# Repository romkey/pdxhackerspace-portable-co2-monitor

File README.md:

# Build Your Own Portable CO2 Monitor

Build Your Own Portable CO2 Monitor is a [PDX Hackerspace] project.

## Design Goals

- minimize cost
- true CO2 measurement
- choice of displays
- optional Home Assistant integration
- optional battery operation
- version that people who are inexperienced with soldering can build
- more integrated version for people who can assemble surface mount hardware
- open source software and hardware

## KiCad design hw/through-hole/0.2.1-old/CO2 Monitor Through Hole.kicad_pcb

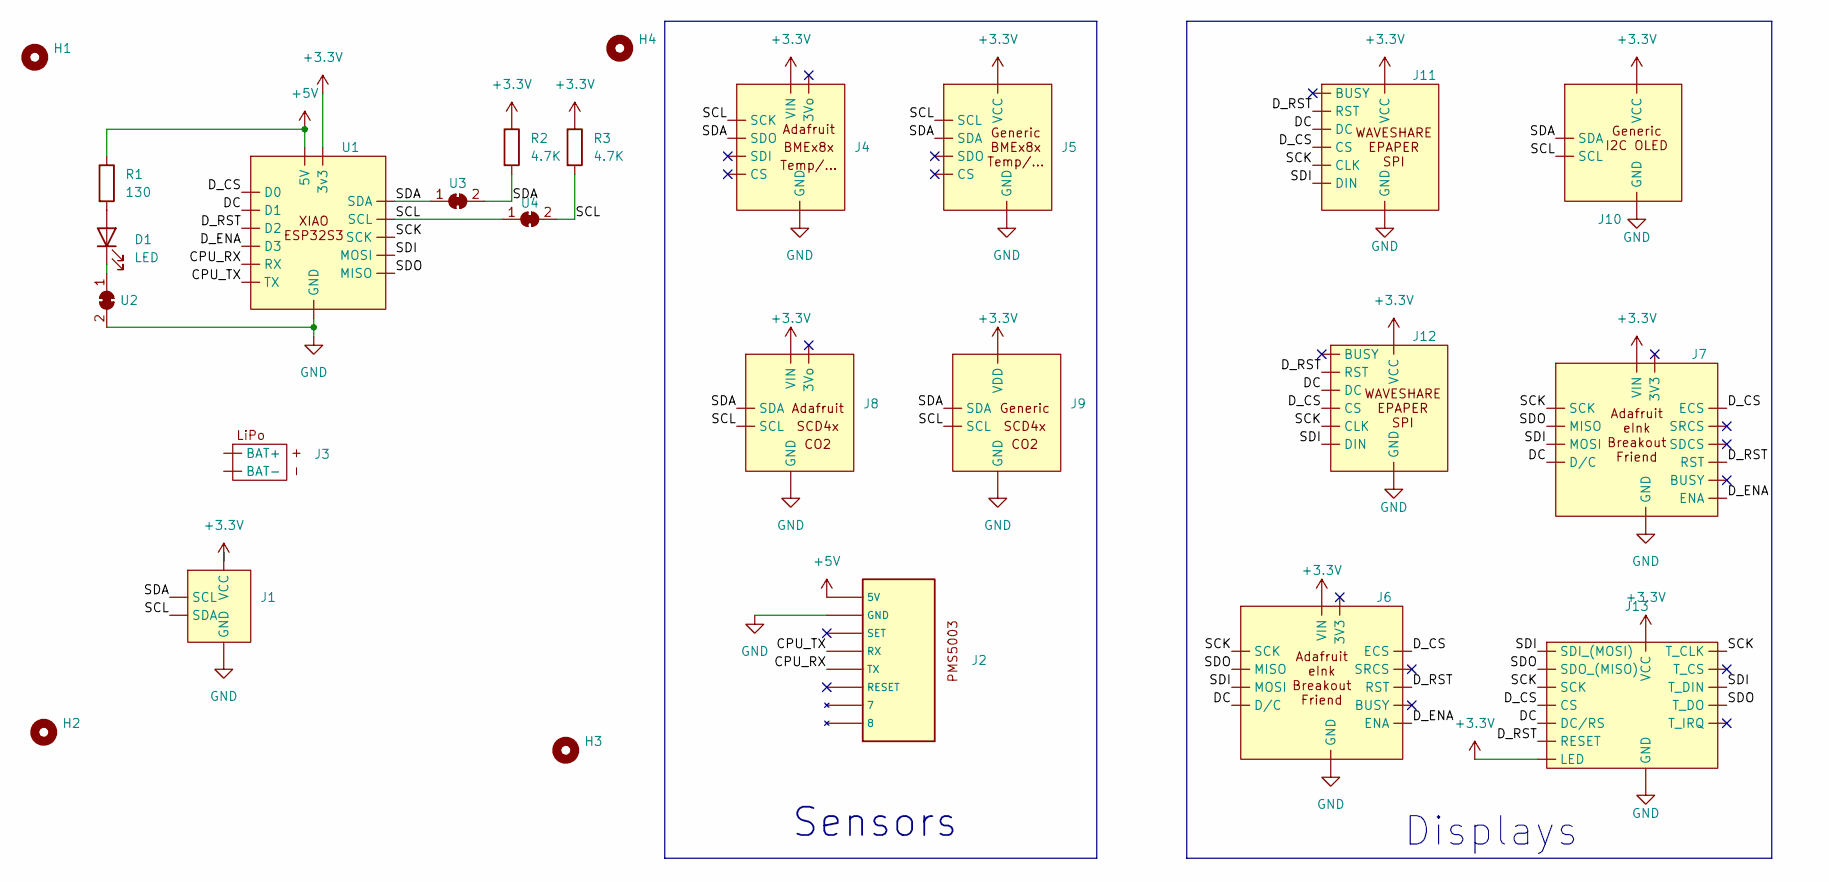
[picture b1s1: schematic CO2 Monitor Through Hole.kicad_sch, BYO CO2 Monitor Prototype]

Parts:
D1: LED; LED_D3.0mm
H1, H2, H3, H4: MountingHole; MountingHole_2.7mm_M2.5
J1: JST_SH_SM04B-SRSS-TB_1x04-1MP_P1.00mm_Horizontal
J2: PMS5003 Connector
J3: LiPo Connector
J4: Adafruit BMx8x Breakout
J5: Generic BMx8x Breakout
J6: Adafruit eInk Breakout Friend
J7: Adafruit eInk Breakout (GENERIC)
J8: Adafruit SCD4x Breakout
J9: Generic SCD4x Breakout
J10: Generic I2C OLED
J11: Wavshare ePaper SPI
J12: Waveshare ePaper SPI JST
J13: SPI_TFT_TOUCH
R1: 130; R_Axial_DIN0207_L6.3mm_D2.5mm_P7.62mm_Horizontal
R2, R3: 4.7K; R_Axial_DIN0207_L6.3mm_D2.5mm_P7.62mm_Horizontal
U1: Xiao ESP32S3
U2, U3, U4: SolderJumper-2_P1.3mm_Bridged_RoundedPad1.0x1.5mm

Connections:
+3.3V: J1.2 (VCC), J4.1 (VIN), J5.1 (VCC), J6.1 (VIN), J7.1 (VIN), J8.1 (VIN), J9.2 (VDD), J10.4 (VCC), J11.8 (VCC), J12.8 (VCC), J13.1 (VCC), J13.8 (LED), R2.1, R3.1, U1.12 (3v3)
+5V: J2.1 (5V), R1.1, U1.14 (5V)
/CPU_RX: J2.5 (TX), U1.8 (RX)
/CPU_TX: J2.4 (RX), U1.7 (TX)
/DC: J6.8 (D/C), J7.8 (D/C), J11.3 (DC), J12.3 (DC), J13.5 (DC/RS), U1.2 (D1)
/D_CS: J6.7 (ECS), J7.7 (ECS), J11.4 (CS), J12.4 (CS), J13.3 (CS), U1.1 (D0)
/D_ENA: J6.12 (ENA), J7.13 (ENA), U1.4 (D3)
/D_RST: J6.10 (RST), J7.11 (RST), J11.2 (RST), J12.2 (RST), J13.4 (RESET), U1.3 (D2)
/SCK: J6.4 (SCK), J7.4 (SCK), J11.5 (CLK), J12.5 (CLK), J13.7 (SCK), J13.10 (T_CLK), U1.9 (SCK)
/SCL: J1.3 (SDA), J4.4 (SCK), J5.3 (SCL), J8.4 (SCL), J9.3 (SCL), J10.2 (SCL), R3.2, U1.6 (SCL), U4.1 (A), U4.2 (B)
/SDA: J1.4 (SCL), J4.5 (SDO), J5.4 (SDA), J8.5 (SDA), J9.4 (SDA), J10.1 (SDA), R2.2, U1.5 (SDA), U3.1 (A), U3.2 (B)
/SDI: J6.6 (MOSI), J7.6 (MOSI), J11.6 (DIN), J12.6 (DIN), J13.6 (SDI_(MOSI)), J13.12 (T_DIN), U1.11 (MOSI)
/SDO: J6.5 (MISO), J7.5 (MISO), J13.9 (SDO_(MISO)), J13.13 (T_DO), U1.10 (MISO)
GND: J1.1 (GND), J2.2 (GND), J4.3 (GND), J5.2 (GND), J6.3 (GND), J7.3 (GND), J8.3 (GND), J9.1 (GND), J10.3 (GND), J11.7 (GND), J12.7 (GND), J13.2 (GND), U1.13 (GND), U2.2 (B)
unnamed: D1.2 (A), R1.2
unnamed: D1.1 (K), U2.1 (A)

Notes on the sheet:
Sensors
Displays

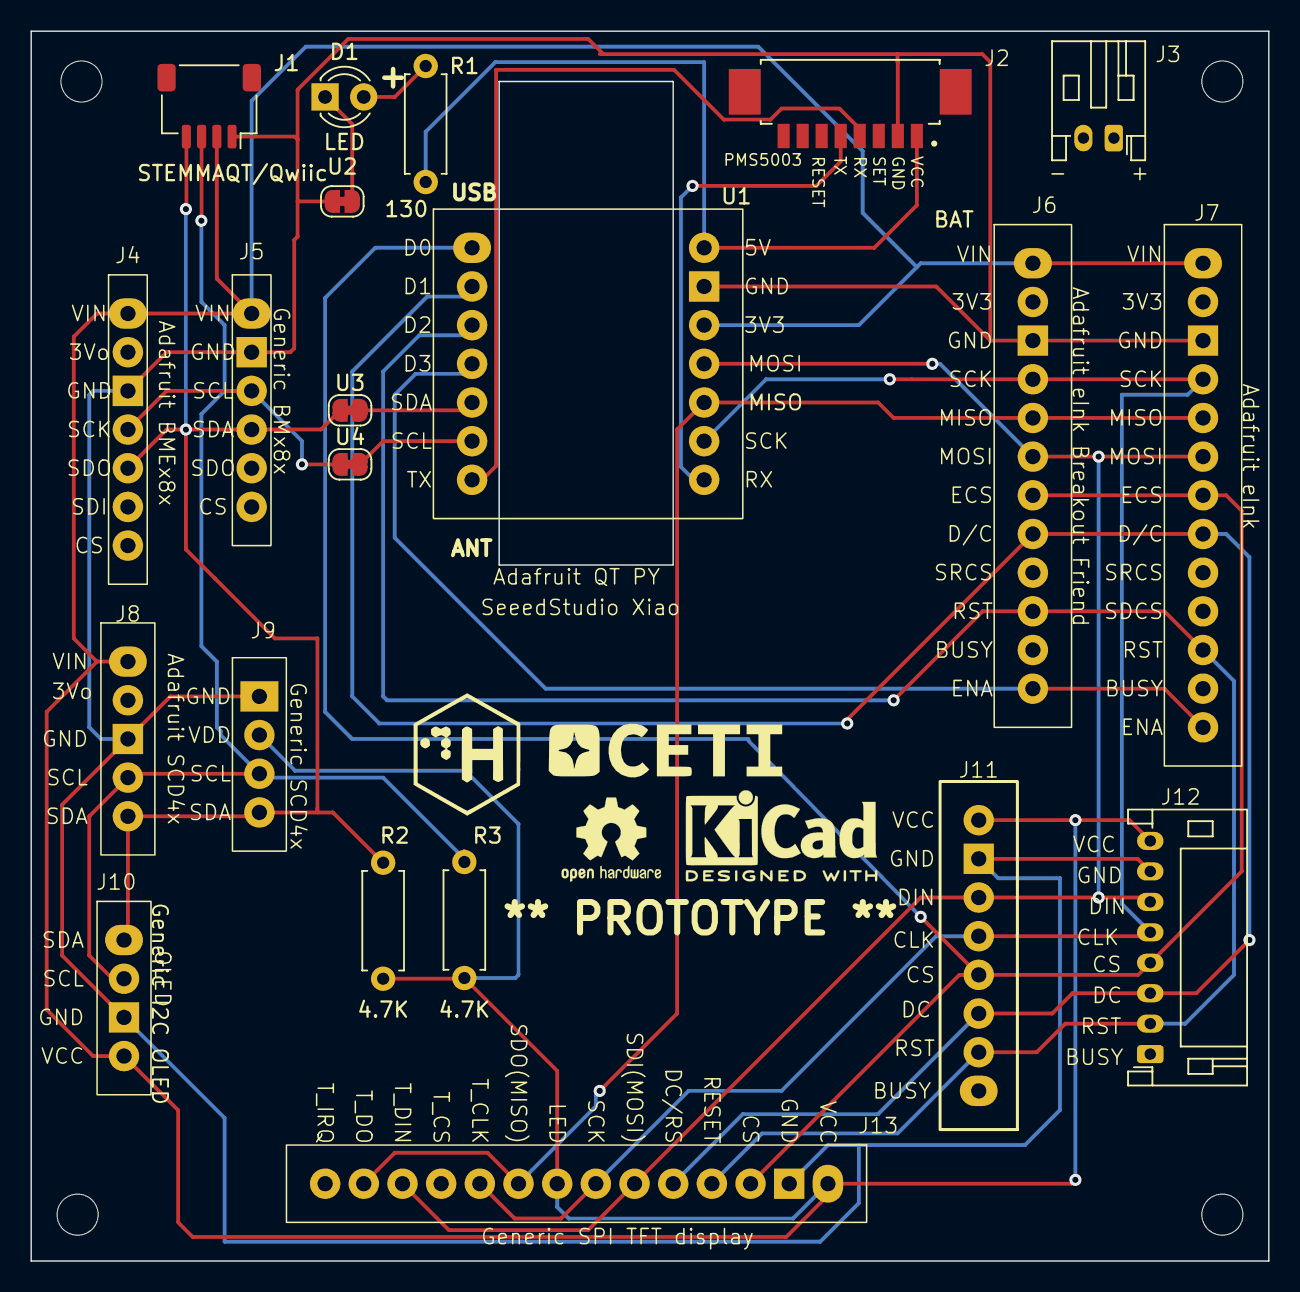
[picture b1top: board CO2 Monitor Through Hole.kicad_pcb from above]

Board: 2 copper layers, 81.3 x 80.8 mm, 25 parts (0 on the bottom side), 16 nets.

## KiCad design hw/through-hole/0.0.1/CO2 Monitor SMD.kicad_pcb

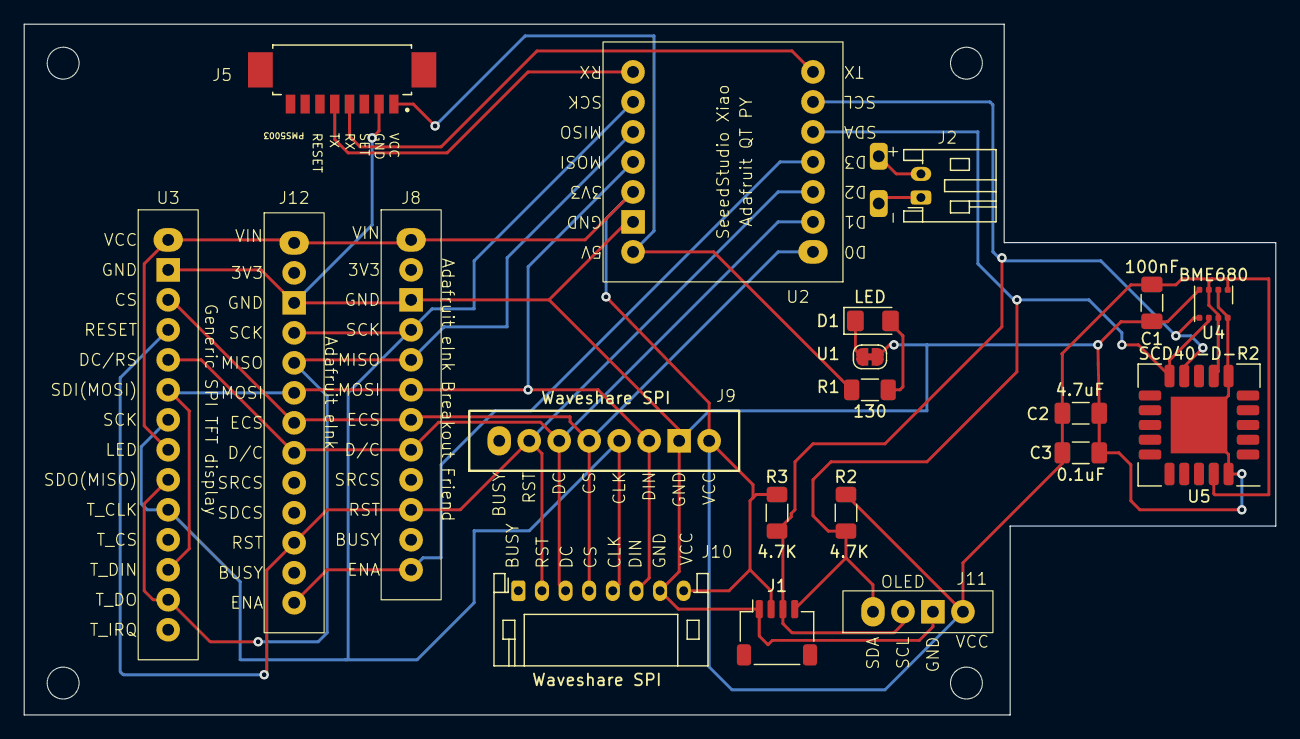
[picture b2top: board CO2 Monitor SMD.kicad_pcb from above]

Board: 2 copper layers, 106.0 x 58.5 mm, 25 parts (0 on the bottom side), 18 nets.

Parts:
C1: 100nF; C_1206_3216Metric_Pad1.33x1.80mm_HandSolder
C2: 4.7uF; C_1206_3216Metric_Pad1.33x1.80mm_HandSolder
C3: 0.1uF; C_1206_3216Metric_Pad1.33x1.80mm_HandSolder
D1: LED; LED_1206_3216Metric_Pad1.42x1.75mm_HandSolder
H1, H2, H3, H4: MountingHole; MountingHole_2.7mm_M2.5
J1: JST_SH_SM04B-SRSS-TB_1x04-1MP_P1.00mm_Horizontal
J2: LiPo Connector
J3: Conn_01x02; LiPo Pads
J5: PMS5003 Connector
J8: Adafruit eInk Breakout Friend
J9: Wavshare ePaper SPI
J10: Waveshare ePaper SPI JST
J11: Generic I2C OLED
J12: Adafruit eInk Breakout (GENERIC)
R1: 130; R_1206_3216Metric_Pad1.30x1.75mm_HandSolder
R2, R3: 4.7K; R_1206_3216Metric_Pad1.30x1.75mm_HandSolder
U1: SolderJumper-2_P1.3mm_Bridged_RoundedPad1.0x1.5mm
U2: Xiao ESP32S3
U3: SPI_TFT_TOUCH
U4: BME680; Bosch_LGA-8_3x3mm_P0.8mm_ClockwisePinNumbering
U5: SCD40-D-R2; Sensirion_SCD4x-1EP_10.1x10.1mm_P1.25mm_EP4.8x4.8mm

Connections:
+3.3V: C1.1, C2.1, C3.1, J1.2 (VCC), J8.1 (VIN), J9.8 (VCC), J10.8 (VCC), J11.4 (VCC), J12.1 (VIN), R2.1, R3.1, U2.12 (3v3), U3.1 (VCC), U3.8 (LED), U4.2 (CSB), U4.6 (VDDIO), U4.8 (VDD), U5.7 (VDD), U5.19 (VDD)
+5V: J5.1 (5V), R1.1, U2.14 (5V)
/CPU_RX: J5.5 (TX), U2.8 (RX)
/CPU_TX: J5.4 (RX), U2.7 (TX)
/DC: J8.8 (D/C), J9.3 (DC), J10.3 (DC), J12.8 (D/C), U2.2 (D1), U3.5 (DC/RS)
/D_CS: J8.7 (ECS), J9.4 (CS), J10.4 (CS), J12.7 (ECS), U2.1 (D0), U3.3 (CS)
/D_ENA: J8.12 (ENA), J12.13 (ENA), U2.4 (D3)
/D_RST: J8.10 (RST), J9.2 (RST), J10.2 (RST), J12.11 (RST), U2.3 (D2), U3.4 (RESET)
/SCK: J8.4 (SCK), J9.5 (CLK), J10.5 (CLK), J12.4 (SCK), U2.9 (SCK), U3.7 (SCK), U3.10 (T_CLK)
/SCL: J1.3 (SDA), J11.2 (SCL), R3.2, U2.6 (SCL), U4.4 (SCK), U5.9 (SCL)
/SDA: J1.4 (SCL), J11.1 (SDA), R2.2, U2.5 (SDA), U4.3 (SDI), U5.10 (SDA)
/SDI: J8.6 (MOSI), J9.6 (DIN), J10.6 (DIN), J12.6 (MOSI), U2.11 (MOSI), U3.6 (SDI_(MOSI)), U3.12 (T_DIN)
/SDO: J8.5 (MISO), J12.5 (MISO), U2.10 (MISO), U3.9 (SDO_(MISO)), U3.13 (T_DO)
GND: C1.2, C2.2, C3.2, J1.1 (GND), J5.2 (GND), J8.3 (GND), J9.7 (GND), J10.7 (GND), J11.3 (GND), J12.3 (GND), U1.2 (B), U2.13 (GND), U3.2 (GND), U4.1 (GND), U4.5 (SDO), U4.7 (GND), U5.6 (GND), U5.20 (GND), U5.21 (GND)
unnamed: D1.2 (A), R1.2
unnamed: D1.1 (K), U1.1 (A)
unnamed: J2.2 (BAT+), J3.2
unnamed: J2.1 (BAT-), J3.1

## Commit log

2023-10-13 added prototype esphome.yml
2023-10-13 fixed graph display in prototype
2024-07-14 added latest KiCAD projects, datasheets, updated esphome code
2024-07-23 test version of 0.2.0 prototype hardware
2024-07-23 minor silkscreen updates
2024-07-24 version 0.2.1 of the hardware
2024-08-02 updated 0.2.1 hardware
    added software tests
2024-08-03 example of simple LCARS interface
